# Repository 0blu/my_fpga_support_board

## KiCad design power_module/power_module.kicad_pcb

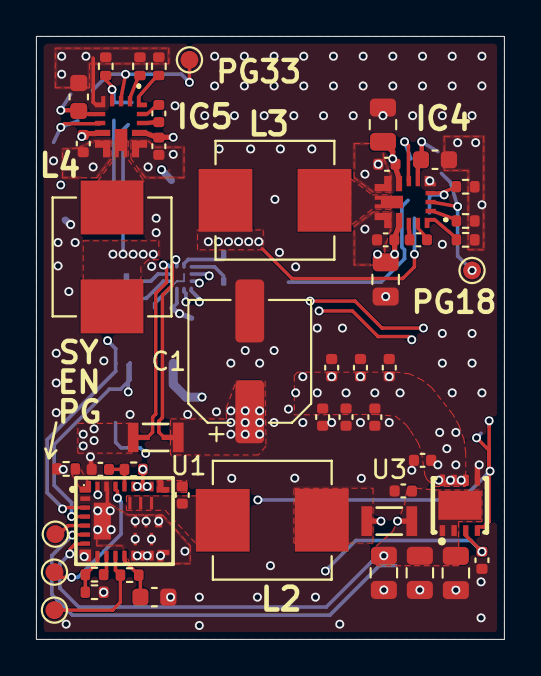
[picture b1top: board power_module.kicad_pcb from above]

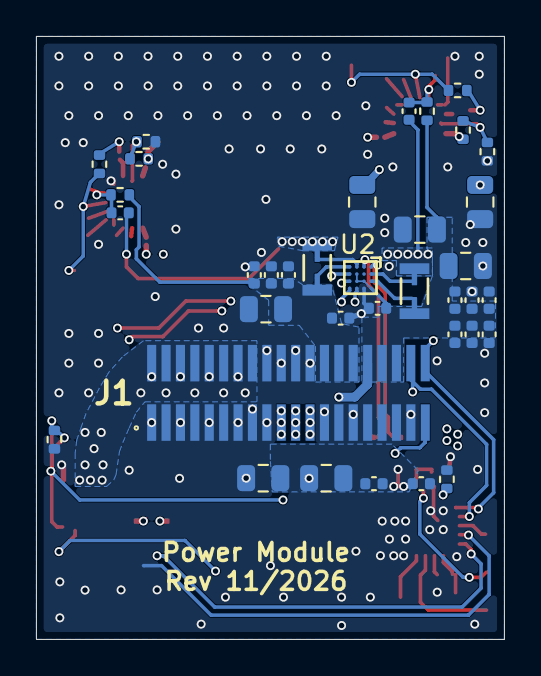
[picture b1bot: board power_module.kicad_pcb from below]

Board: 4 copper layers, 26.0 x 33.5 mm, 88 parts (37 on the bottom side), 49 nets.

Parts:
C1: 47uF 25V; CP_Elec_6.3x5.4
C22, C23, C29, C30, C36, C37: 10uF 25V; C_0805_2012Metric
C24: 1uF 25V; C_0402_1005Metric
C25, C33, C40: 4.7uF 16V; C_0603_1608Metric
C26, C27, C31, C32, C38, C39, C45, C46, C49, C50, C53, C54, C55, C56, C57, C59, C60, C62, C63, C64, C65, C72: 47nF 50V; C_0402_1005Metric
C28, C34, C41, C73, C74: 100nF 50V; C_0402_1005Metric
C35, C42: 20pF 50V; C_0402_1005Metric
C44, C47, C48: 22uF 10V; C_0805_2012Metric
C51, C52: 10uF 6.3V; C_0402_1005Metric
C75, C76, C77: 100uF 6.3V; C_0805_2012Metric
IC4, IC5: TPS543820RPYR
J1: FTE-120-01-G-DV
L2: 220nH; WE_L_744373460022
L3, L4: 1.0uH; WE_L_74437349010
NT1: NetTie_2; NetTie-2_SMD_Pad0.2mm
R24: 10R 1%; R_0402_1005Metric
R25, R39, R41, R46, R48: 10k 1%; R_0402_1005Metric
R27: 110k 0.1%; R_0402_1005Metric
R28: 20k 0.1%; R_0402_1005Metric
R29, R40: 26.1k 1%; R_0402_1005Metric
R30: 47.5k 1%; R_0402_1005Metric
R31, R32, R33, R34: 0.002R; shunt_1206in_3216mm
R35, R42: 16.9k 1%; R_0402_1005Metric
R36, R43: 6.8k 1%; R_0402_1005Metric
R37: 26.7k 1%; R_0402_1005Metric
R38, R45: 8.06k 1%; R_0402_1005Metric
R44: 60.4k 1%; R_0402_1005Metric
R47: 56k 1%; R_0402_1005Metric
R49: 100k 1%; R_0402_1005Metric
TP1: TP_PGDYN; TestPoint_Pad_D1.0mm
TP2: TP_EN; TestPoint_Pad_D1.0mm
TP3: TP_SYNC; TestPoint_Pad_D1.0mm
TP4: TP_PG3V3; TestPoint_Pad_D1.0mm
TP5: TP_PG1V8; TestPoint_Pad_D1.0mm
U1: TPS542A50
U2: INA4230AIYBJR
U3: TPS22959; TPS22959DNYR

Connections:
/+1.8V: C44.1, C45.1, C46.1, C59.1, C60.1, J1.26, J1.28, J1.30, R32.1, R40.2
/+3.3V: C47.1, C48.1, C49.1, C50.1, C62.1, C63.1, C64.1, C65.1, C73.1, C74.1, J1.32, J1.34, J1.36, R33.1, R47.2, U2.A4 (VS), U2.B3 (EN), U2.C2 (A0), U2.C3 (A1), U3.3 (VBIAS)
/+RAW_VIN: C1.1, J1.19, J1.21, J1.23, R31.4
/DYN_V: C72.1, C75.1, C76.1, C77.1, R34.1, U1.7 (RSP), U3.1 (VIN), U3.2 (VIN), U3.9 (VIN)
/DYN_V_EN: J1.39, R49.1, U3.4 (ON)
/DYN_V_EXT: C51.1, C52.1, C53.1, C54.1, C55.1, C56.1, C57.1, J1.2, J1.4, J1.6, J1.8, J1.10, J1.12, J1.14, J1.16, U3.6 (VOUT), U3.7 (VOUT), U3.8 (VOUT)
/Dynamic Power Conversion/+VIN: C22.1, C23.1, C26.1, C27.1, C29.1, C30.1, C31.1, C32.1, C36.1, C37.1, C38.1, C39.1, IC4.8 (VIN), IC4.12 (VIN_2), IC5.8 (VIN), IC5.12 (VIN_2), R24.1, R31.1, R35.2, R42.2, U1.18 (PVIN), U1.19 (PVIN), U1.20 (PVIN)
/Dynamic Power Conversion/BOOT: C28.1, U1.17 (BOOT)
/Dynamic Power Conversion/COMP: R29.2, U1.24 (COMP)
/Dynamic Power Conversion/DYN_RSN: NT1.1, U1.6 (RSN)
/Dynamic Power Conversion/EN: TP2.1 (1_1), U1.22 (EN)
/Dynamic Power Conversion/PGD: R25.2, TP1.1 (1_1), U1.11 (PGD)
/Dynamic Power Conversion/SREF: R27.2, U1.10 (SREF)
/Dynamic Power Conversion/SW: C28.2, L2.1, U1.26 (SW), U1.27 (SW), U1.28 (SW)
/Dynamic Power Conversion/SYNC: TP3.1 (1_1), U1.5 (SYNC)
/Dynamic Power Conversion/VREG: C25.1, R25.1, U1.12 (VREG)
/Dynamic Power Conversion/VSET: R27.1, R28.2, U1.9 (VSET)
/Measurement/MES_1.8_N: R32.2, U2.D1 (IN+3)
/Measurement/MES_1.8_P: R32.3, U2.C1 (IN–3)
/Measurement/MES_3.3_N: R33.2, U2.A3 (IN+1)
/Measurement/MES_3.3_P: R33.3, U2.A2 (IN–1)
/Measurement/MES_DYN_N: R34.2, U2.D2 (IN–4)
/Measurement/MES_DYN_P: R34.3, U2.D3 (IN+4)
/Measurement/MES_VIN_N: R31.2, U2.A1 (IN+2)
/Measurement/MES_VIN_P: R31.3, U2.B1 (IN–2)
/RAW_1.8V: C35.1, L3.2, R32.4
/RAW_3.3V: C42.1, L4.2, R33.4
/RAW_DYN_V: L2.2, R34.4
GND: C1.2, C22.2, C23.2, C24.2, C25.2, C26.2, C27.2, C29.2, C30.2, C31.2, C32.2, C33.2, C36.2, C37.2, C38.2, C39.2, C40.2, C44.2, C45.2, C46.2, C47.2, C48.2, C49.2, C50.2, C51.2, C52.2, C53.2, C54.2, C55.2, C56.2, C57.2, C59.2, C60.2, C62.2, C63.2, C64.2, C65.2, C72.2, C73.2, C74.2, C75.2, C76.2, C77.2, IC4.5 (AGND), IC4.9 (PGND), IC4.11 (PGND_2), IC4.16 (AGND_2), IC4.17 (PGND_3), IC4.20 (PGND_4), IC5.5 (AGND), IC5.9 (PGND), IC5.11 (PGND_2), IC5.16 (AGND_2), IC5.17 (PGND_3), IC5.20 (PGND_4), J1.1, J1.3, J1.5, J1.7, J1.9, J1.11, J1.13, J1.15, J1.17, J1.18, J1.20, J1.22, J1.24, J1.25, J1.27, J1.29, J1.31, J1.33, J1.35, J1.37, NT1.2, R28.1, R29.1, R30.1, R36.1, R37.1, R38.1, R41.1, R43.1, R44.1, R45.1, R48.1, R49.2, U1.2 (SS/PFM), U1.8 (AGND), U1.13 (PGND), U1.14 (PGND), U1.15 (PGND), U1.16 (PGND), U1.23 (FSEL), U1.25 (AGND), U1.29 (PGND), U1.30 (PGND), U1.31 (PGND), U1.32 (PGND), U1.33 (PGND), U2.B4 (GND), U3.5 (GND)
I2C_PM_SCL: J1.40, U1.3 (SCL), U2.C4 (SCL)
I2C_PM_SDA: J1.38, U1.4 (SDA), U2.D4 (SDA)
unnamed: C34.1, IC4.14 (BOOT)
unnamed: C33.1, IC4.6 (BP5), R39.1
unnamed: IC4.7 (EN), R35.1, R36.2
unnamed: C35.2, IC4.4 (FB), R40.1, R41.2
unnamed: IC4.2 (MODE), R37.2
unnamed: IC4.3 (PGOOD), R39.2, TP5.1 (1_1)
unnamed: C34.2, IC4.10 (SW), IC4.13 (SW_13), IC4.18 (SW_3), IC4.19 (SW_4), L3.1
unnamed: IC4.1 (SYNC/_FSEL), IC4.15 (SYNC/_FSEL_2), R38.2
unnamed: C41.1, IC5.14 (BOOT)
unnamed: C40.1, IC5.6 (BP5), R46.1
unnamed: IC5.7 (EN), R42.1, R43.2
unnamed: C42.2, IC5.4 (FB), R47.1, R48.2
unnamed: IC5.2 (MODE), R44.2
unnamed: IC5.3 (PGOOD), R46.2, TP4.1 (1_1)
unnamed: C41.2, IC5.10 (SW), IC5.13 (SW_13), IC5.18 (SW_3), IC5.19 (SW_4), L4.1
unnamed: IC5.1 (SYNC/_FSEL), IC5.15 (SYNC/_FSEL_2), R45.2
unnamed: C24.1, R24.2, U1.21 (AVIN)
unnamed: R30.2, U1.1 (ILIM)

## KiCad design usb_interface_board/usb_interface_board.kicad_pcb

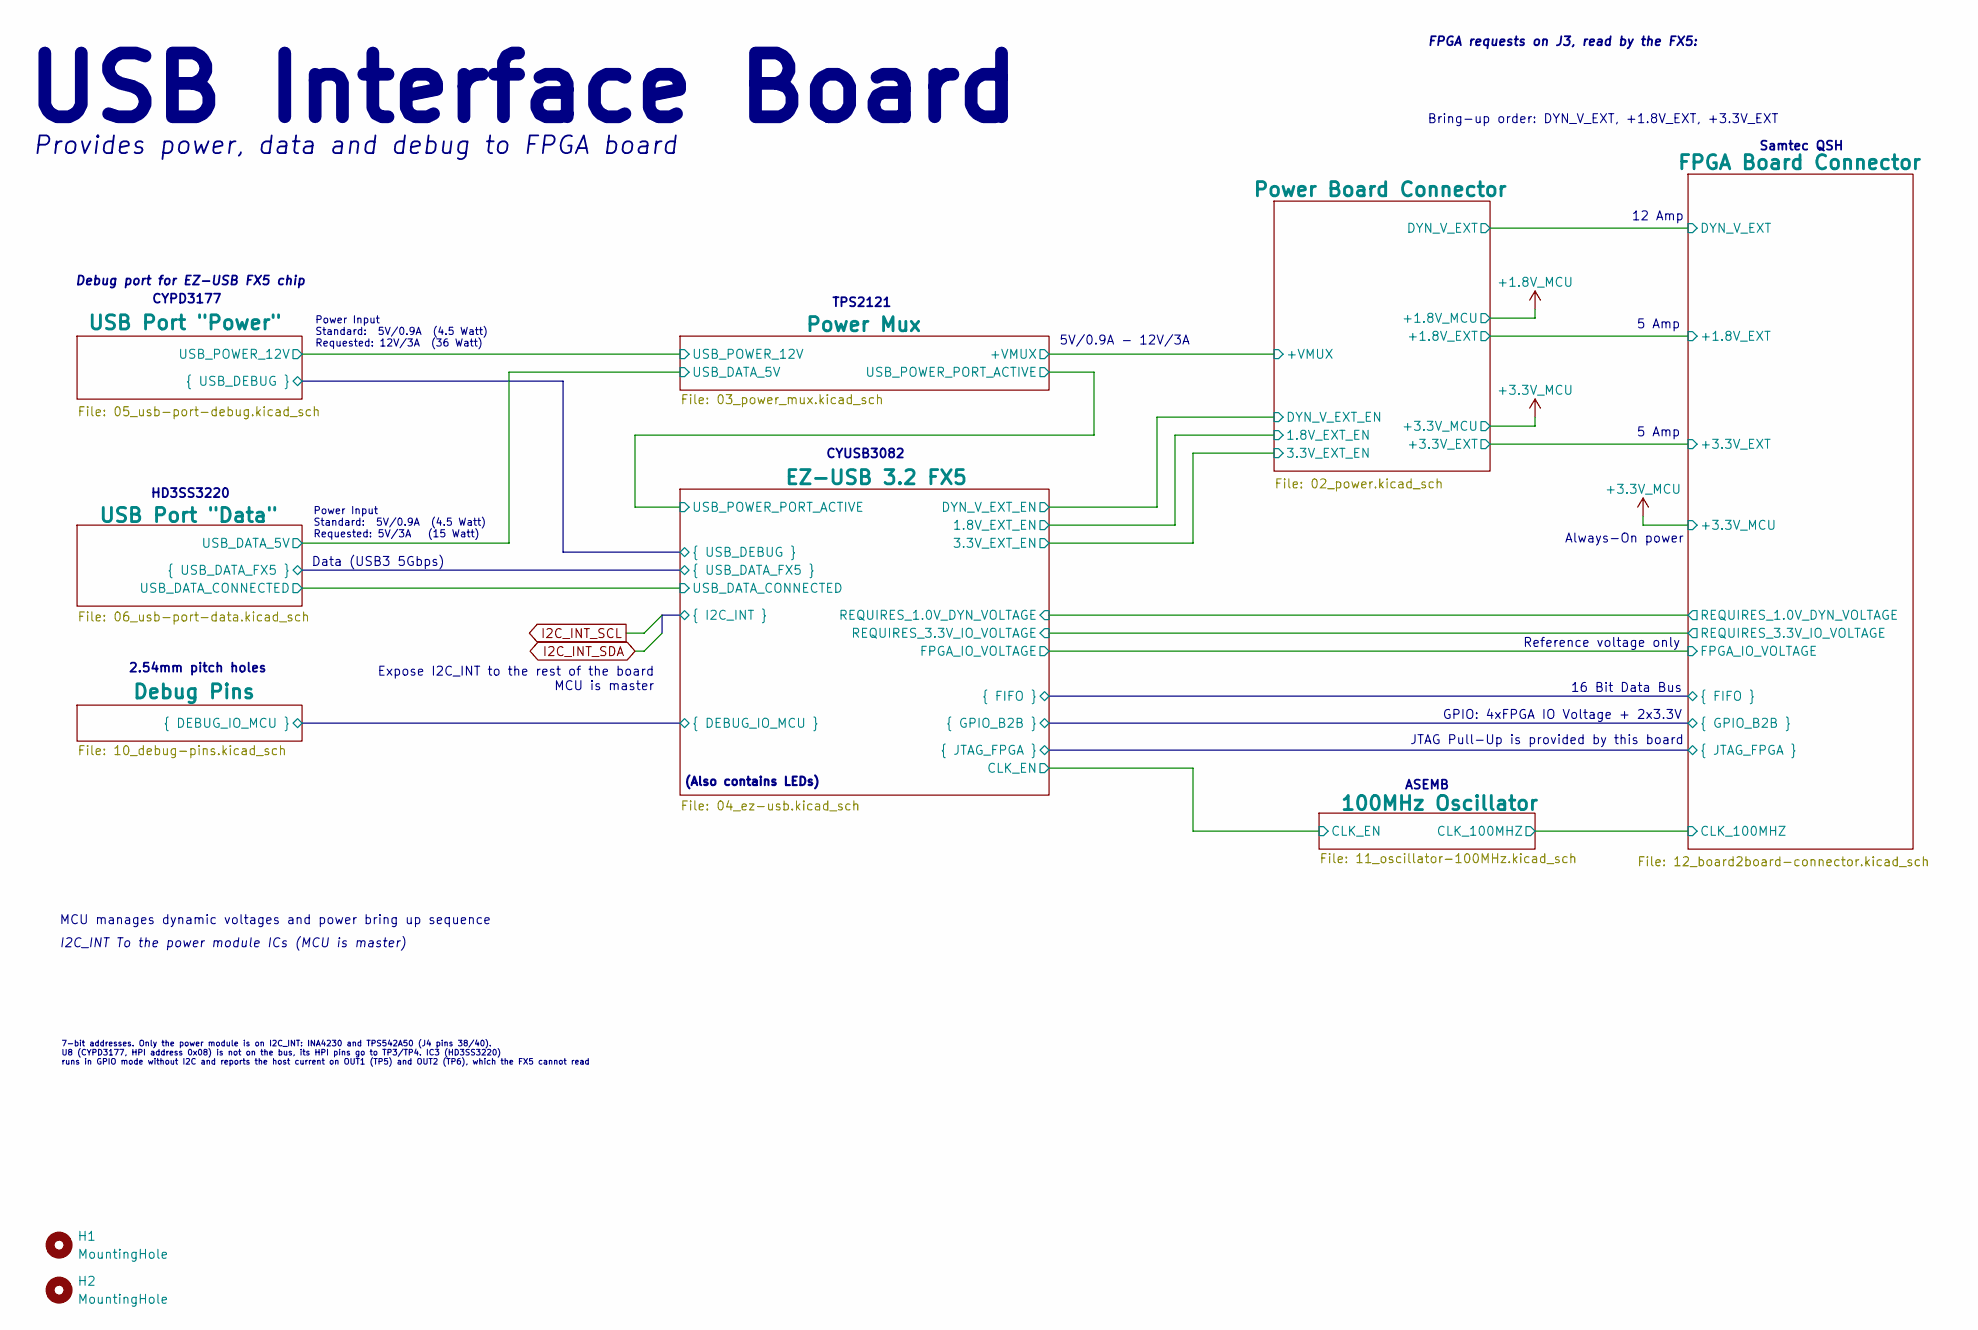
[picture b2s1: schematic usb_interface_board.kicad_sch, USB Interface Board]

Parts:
H1, H2: MountingHole; MountingHole_2.2mm_M2

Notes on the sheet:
MCU manages dynamic voltages and power bring up sequence
16 Bit Data Bus
ASEMB
Debug port for EZ-USB FX5 chip
(Also contains LEDs)
Power Input Standard: 5V/0.9A (4.5 Watt) Requested: 5V/3A (15 Watt)
CYUSB3082
USB Interface Board
Bring-up order: DYN_V_EXT, +1.8V_EXT, +3.3V_EXT
GPIO: 4xFPGA IO Voltage + 2x3.3V
Always-On power
Expose I2C_INT to the rest of the board MCU is master
CYPD3177
5 Amp
Samtec QSH
JTAG Pull-Up is provided by this board
2.54mm pitch holes
TPS2121
5V/0.9A - 12V/3A
Power Input Standard: 5V/0.9A (4.5 Watt) Requested: 12V/3A (36 Watt)
Reference voltage only
HD3SS3220
Data (USB3 5Gbps)
12 Amp
FPGA requests on J3, read by the FX5:
Provides power, data and debug to FPGA board
I2C_INT To the power module ICs (MCU is master)
7-bit addresses. Only the power module is on I2C_INT: INA4230 and TPS542A50 (J4 pins 38/40). U8 (CYPD3177, HPI address 0x08) is not on the bus, its HPI pins go to TP3/TP4. IC3 (HD3SS3220) runs in GPIO mode without I2C and reports the host current on OUT1 (TP5) and OUT2 (TP6), which the FX5 cannot r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

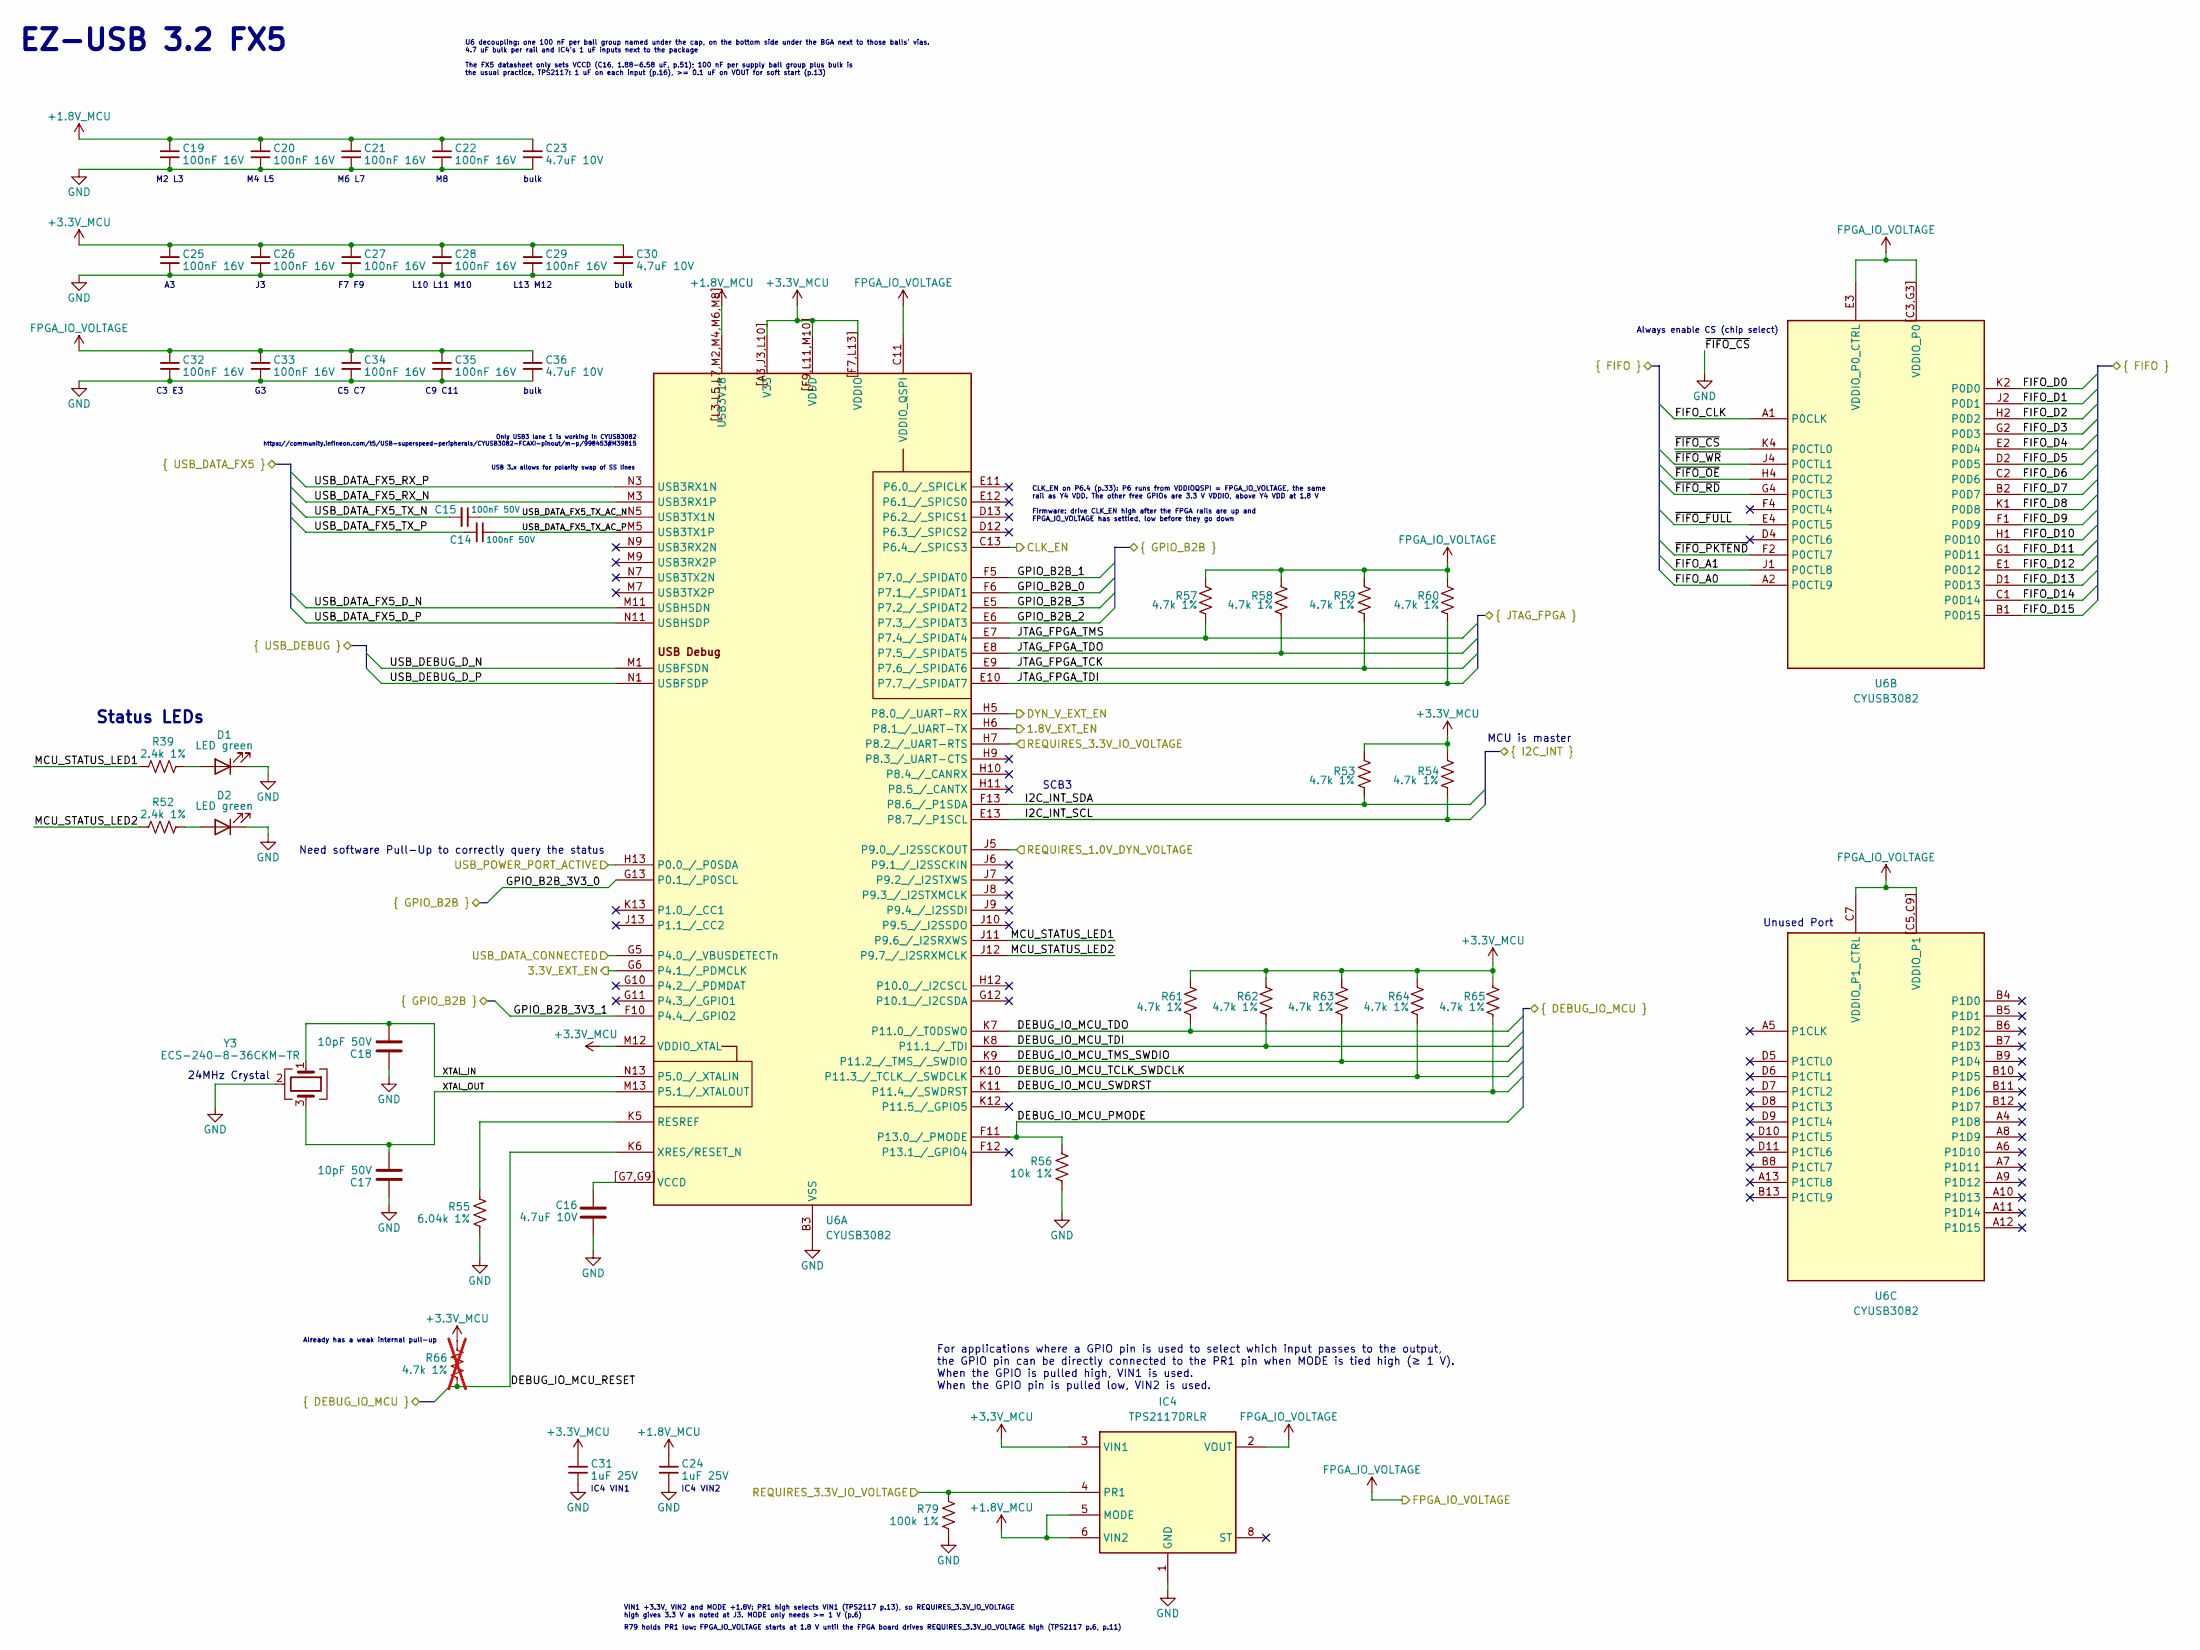
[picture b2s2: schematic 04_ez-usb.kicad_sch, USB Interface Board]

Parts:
C14, C15: 100nF 50V; C_0402_1005Metric; Manufacturer Part CL05B104KB54PNC; LCSC C307331
C16, C23, C30, C36: 4.7uF 10V; C_0402_1005Metric; Manufacturer Part CL05A475MP5NRNC; LCSC C23733
C17, C18: 10pF 50V; C_0402_1005Metric; Manufacturer Part CL05C100JB5NNNC; LCSC C32949
C19, C20, C21, C22, C25, C26, C27, C28, C29, C32, C33, C34, C35: 100nF 16V; C_0201_0603Metric; Manufacturer Part CL03A104KO3NNNC; LCSC C307380
C24, C31: 1uF 25V; C_0402_1005Metric; Manufacturer Part CL05A105KA5NQNC; LCSC C52923
D1, D2: LED green; LED_0805_2012Metric; Manufacturer Part LTST-C170KGKT; LCSC C98221
IC4: TPS2117DRLR; SOTFL50P160X60-8N; Mouser Part Number 595-TPS2117DRLR
R39, R52: 2.4k 1%; R_0402_1005Metric; Manufacturer Part RC0402FR-072K4L; LCSC C112296
R53, R54, R57, R58, R59, R60, R61, R62, R63, R64, R65: 4.7k 1%; R_0402_1005Metric; Manufacturer Part 0402WGF4701TCE; LCSC C25900
R55: 6.04k 1%; R_0402_1005Metric; Manufacturer Part RC0402FR-076K04L; LCSC C97819
R56: 10k 1%; R_0402_1005Metric; Manufacturer Part 0402WGF1002TCE; LCSC C25744
R66: 4.7k 1%; R_0402_1005Metric; Manufacturer Part 0402WGF4701TCE; LCSC C25900; not fitted
R79: 100k 1%; R_0402_1005Metric; Manufacturer Part 0402WGF1003TCE; LCSC C25741
U6: CYUSB3082; Infineon_TFBGA-169_10x10mm_Layout13x13_P0.75mm; Manufacturer Part CYUSB3082-FCAXI
Y3: ECS-240-8-36CKM-TR; Manufacturer Part ECS-240-8-36CKM-TR; LCSC C435195

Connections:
+1.8V_MCU: C19.1, C20.1, C21.1, C22.1, C23.1, C24.1, IC4.5 (MODE), IC4.6 (VIN2), U6.L3 (USB3V18), U6.L5 (USB3V18), U6.L7 (USB3V18), U6.M2 (USB3V18), U6.M4 (USB3V18), U6.M6 (USB3V18), U6.M8 (USB3V18), U6.[L3,L5,L7,M2,M4,M6,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 (USB3V18); also elsewhere on the board
+3.3V_MCU: C25.1, C26.1, C27.1, C28.1, C29.1, C30.1, C31.1, IC4.3 (VIN1), R53.1, R54.1, R61.1, R62.1, R63.1, R64.1, R65.1, R66.1, U6.A3 (V33), U6.F7 (VDDIO), U6.F9 (VDDD), U6.J3 (V33), U6.L10 (V33), U6.L11 (VDDD), U6.L13 (VDDIO), U6.M10 (VDDD), U6.M12 (VDDIO_XTAL), U6.[A3,J3,L10] (V33), U6.[F7,L13] (VDDIO), U6.[F9,L11,M10] (VDDD); also elsewhere on the board
/100MHz Oscillator/CLK_EN: U6.C13 (P6.4_/_SPICS3); also elsewhere on the board
/Debug Pins/DEBUG_IO_MCU_PMODE: R56.1, U6.F11 (P13.0_/_PMODE); also elsewhere on the board
/Debug Pins/DEBUG_IO_MCU_RESET: R66.2, U6.K6 (XRES/RESET_N); also elsewhere on the board
/Debug Pins/DEBUG_IO_MCU_SWDRST: R65.2, U6.K11 (P11.4_/_SWDRST); also elsewhere on the board
/Debug Pins/DEBUG_IO_MCU_TCLK_SWDCLK: R64.2, U6.K10 (P11.3_/_TCLK_/_SWDCLK); also elsewhere on the board
/Debug Pins/DEBUG_IO_MCU_TDI: R62.2, U6.K8 (P11.1_/_TDI); also elsewhere on the board
/Debug Pins/DEBUG_IO_MCU_TDO: R61.2, U6.K7 (P11.0_/_T0DSWO); also elsewhere on the board
/Debug Pins/DEBUG_IO_MCU_TMS_SWDIO: R63.2, U6.K9 (P11.2_/_TMS_/_SWDIO); also elsewhere on the board
/EZ-USB 3.2 FX5/1.8V_EXT_EN: U6.H6 (P8.1_/_UART-TX); also elsewhere on the board
/EZ-USB 3.2 FX5/3.3V_EXT_EN: U6.G6 (P4.1_/_PDMCLK); also elsewhere on the board
/EZ-USB 3.2 FX5/DYN_V_EXT_EN: U6.H5 (P8.0_/_UART-RX); also elsewhere on the board
/EZ-USB 3.2 FX5/FIFO_A0: U6.A2 (P0CTL9); also elsewhere on the board
/EZ-USB 3.2 FX5/FIFO_A1: U6.J1 (P0CTL8); also elsewhere on the board
/EZ-USB 3.2 FX5/FIFO_CLK: U6.A1 (P0CLK); also elsewhere on the board
/EZ-USB 3.2 FX5/FIFO_D0: U6.K2 (P0D0); also elsewhere on the board
/EZ-USB 3.2 FX5/FIFO_D1: U6.J2 (P0D1); also elsewhere on the board
/EZ-USB 3.2 FX5/FIFO_D2: U6.H2 (P0D2); also elsewhere on the board
/EZ-USB 3.2 FX5/FIFO_D3: U6.G2 (P0D3); also elsewhere on the board
/EZ-USB 3.2 FX5/FIFO_D4: U6.E2 (P0D4); also elsewhere on the board
/EZ-USB 3.2 FX5/FIFO_D5: U6.D2 (P0D5); also elsewhere on the board
/EZ-USB 3.2 FX5/FIFO_D6: U6.C2 (P0D6); also elsewhere on the board
/EZ-USB 3.2 FX5/FIFO_D7: U6.B2 (P0D7); also elsewhere on the board
/EZ-USB 3.2 FX5/FIFO_D8: U6.K1 (P0D8); also elsewhere on the board
/EZ-USB 3.2 FX5/FIFO_D9: U6.F1 (P0D9); also elsewhere on the board
/EZ-USB 3.2 FX5/FIFO_D10: U6.H1 (P0D10); also elsewhere on the board
/EZ-USB 3.2 FX5/FIFO_D11: U6.G1 (P0D11); also elsewhere on the board
/EZ-USB 3.2 FX5/FIFO_D12: U6.E1 (P0D12); also elsewhere on the board
/EZ-USB 3.2 FX5/FIFO_D13: U6.D1 (P0D13); also elsewhere on the board
/EZ-USB 3.2 FX5/FIFO_D14: U6.C1 (P0D14); also elsewhere on the board
/EZ-USB 3.2 FX5/FIFO_D15: U6.B1 (P0D15); also elsewhere on the board
/EZ-USB 3.2 FX5/GPIO_B2B_0: U6.F6 (P7.1_/_SPIDAT1); also elsewhere on the board
/EZ-USB 3.2 FX5/GPIO_B2B_1: U6.F5 (P7.0_/_SPIDAT0); also elsewhere on the board
/EZ-USB 3.2 FX5/GPIO_B2B_2: U6.E6 (P7.3_/_SPIDAT3); also elsewhere on the board
/EZ-USB 3.2 FX5/GPIO_B2B_3: U6.E5 (P7.2_/_SPIDAT2); also elsewhere on the board
/EZ-USB 3.2 FX5/GPIO_B2B_3V3_0: U6.G13 (P0.1_/_P0SCL); also elsewhere on the board
/EZ-USB 3.2 FX5/GPIO_B2B_3V3_1: U6.F10 (P4.4_/_GPIO2); also elsewhere on the board
/EZ-USB 3.2 FX5/JTAG_FPGA_TCK: R59.2, U6.E9 (P7.6_/_SPIDAT6); also elsewhere on the board
/EZ-USB 3.2 FX5/JTAG_FPGA_TDI: R60.2, U6.E10 (P7.7_/_SPIDAT7); also elsewhere on the board
/EZ-USB 3.2 FX5/JTAG_FPGA_TDO: R58.2, U6.E8 (P7.5_/_SPIDAT5); also elsewhere on the board
/EZ-USB 3.2 FX5/JTAG_FPGA_TMS: R57.2, U6.E7 (P7.4_/_SPIDAT4); also elsewhere on the board
/EZ-USB 3.2 FX5/MCU_STATUS_LED1: R39.2, U6.J11 (P9.6_/_I2SRXWS)
/EZ-USB 3.2 FX5/MCU_STATUS_LED2: R52.2, U6.J12 (P9.7_/_I2SRXMCLK)
/EZ-USB 3.2 FX5/REQUIRES_1.0V_DYN_VOLTAGE: U6.J5 (P9.0_/_I2SSCKOUT); also elsewhere on the board
/EZ-USB 3.2 FX5/REQUIRES_3.3V_IO_VOLTAGE: IC4.4 (PR1), R79.1, U6.H7 (P8.2_/_UART-RTS); also elsewhere on the board
/EZ-USB 3.2 FX5/USB_DATA_CONNECTED: U6.G5 (P4.0_/_VBUSDETECTn); also elsewhere on the board
/EZ-USB 3.2 FX5/USB_DATA_FX5_D_N: U6.M11 (USBHSDN); also elsewhere on the board
/EZ-USB 3.2 FX5/USB_DATA_FX5_D_P: U6.N11 (USBHSDP); also elsewhere on the board
/EZ-USB 3.2 FX5/USB_DATA_FX5_RX_N: U6.M3 (USB3RX1P); also elsewhere on the board
/EZ-USB 3.2 FX5/USB_DATA_FX5_RX_P: U6.N3 (USB3RX1N); also elsewhere on the board
/EZ-USB 3.2 FX5/USB_DATA_FX5_TX_AC_N: C15.2, U6.N5 (USB3TX1N)
/EZ-USB 3.2 FX5/USB_DATA_FX5_TX_AC_P: C14.2, U6.M5 (USB3TX1P)
/EZ-USB 3.2 FX5/USB_DATA_FX5_TX_N: C15.1; also elsewhere on the board
/EZ-USB 3.2 FX5/USB_DATA_FX5_TX_P: C14.1; also elsewhere on the board
/EZ-USB 3.2 FX5/USB_DEBUG_D_N: U6.M1 (USBFSDN); also elsewhere on the board
/EZ-USB 3.2 FX5/USB_DEBUG_D_P: U6.N1 (USBFSDP); also elsewhere on the board
/EZ-USB 3.2 FX5/USB_POWER_PORT_ACTIVE: U6.H13 (P0.0_/_P0SDA); also elsewhere on the board
/EZ-USB 3.2 FX5/XTAL_IN: C18.2, U6.N13 (P5.0_/_XTALIN), Y3.1
/EZ-USB 3.2 FX5/XTAL_OUT: C17.2, U6.M13 (P5.1_/_XTALOUT), Y3.3
/EZ-USB 3.2 FX5/~FIFO_FULL: U6.E4 (P0CTL5); also elsewhere on the board
/EZ-USB 3.2 FX5/~FIFO_OE: U6.H4 (P0CTL2); also elsewhere on the board
/EZ-USB 3.2 FX5/~FIFO_PKTEND: U6.F2 (P0CTL7); also elsewhere on the board
/EZ-USB 3.2 FX5/~FIFO_RD: U6.G4 (P0CTL3); also elsewhere on the board
/EZ-USB 3.2 FX5/~FIFO_WR: U6.J4 (P0CTL1); also elsewhere on the board
FPGA_IO_VOLTAGE: C32.1, C33.1, C34.1, C35.1, C36.1, IC4.2 (VOUT), IC4.7 (VOUT_2), R57.1, R58.1, R59.1, R60.1, U6.C3 (VDDIO_P0), U6.C5 (VDDIO_P1), U6.C7 (VDDIO_P1_CTRL), U6.C9 (VDDIO_P1), U6.C11 (VDDIO_QSPI), U6.E3 (VDDIO_P0_CTRL), U6.G3 (VDDIO_P0), U6.[C3,G3] (VDDIO_P0), U6.[C5,C9] (VDDIO_P1); also elsewhere on the board
GND: C16.1, C17.1, C18.1, C19.2, C20.2, C21.2, C22.2, C23.2, C24.2, C25.2, C26.2, C27.2, C28.2, C29.2, C30.2, C31.2, C32.2, C33.2, C34.2, C35.2, C36.2, D1.1 (K), D2.1 (K), IC4.1 (GND), R55.2, R56.2, R79.2, U6.B3 (VSS), U6.C4 (VSS), U6.C6 (VSS), U6.C8 (VSS), U6.C10 (VSS), U6.C12 (VSS), U6.D3 (VSS), U6.F3 (VSS), U6.F8 (VSS), U6.G8 (VSS), U6.H3 (VSS), U6.H8 (VSS), U6.K3 (VSS), U6.K4 (P0CTL0), U6.L1 (VSS), U6.L2 (VSS), U6.L4 (VSS), U6.L6 (VSS), U6.L8 (VSS), U6.L9 (VSS), U6.L12 (VSS), U6.N2 (VSS), U6.N4 (VSS), U6.N6 (VSS), U6.N8 (VSS), U6.N10 (VSS), U6.N12 (VSS), Y3.2 (G), Y3.4 (G); also elsewhere on the board
I2C_INT_SCL: R54.2, U6.E13 (P8.7_/_P1SCL); also elsewhere on the board
I2C_INT_SDA: R53.2, U6.F13 (P8.6_/_P1SDA); also elsewhere on the board
unnamed: D1.2 (A), R39.1
unnamed: D2.2 (A), R52.1
unnamed: R55.1, U6.K5 (RESREF)
unnamed: C16.2, U6.G7 (VCCD), U6.G9 (VCCD), U6.[G7,G9] (VCCD)

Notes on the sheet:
L13 M12
Always enable CS (chip select)
Only USB3 lane 1 is working in CYUSB3082 https://community.infineon.com/t5/USB-superspeed-peripherals/CYUSB3082-FCAXI-pinout/m-p/998453#M39815
24MHz Crystal
Status LEDs
CLK_EN on P6.4 (p.33): P6 runs from VDDIOQSPI = FPGA_IO_VOLTAGE, the same rail as Y4 VDD. The other free GPIOs are 3.3 V VDDIO, above Y4 VDD at 1.8 V
Firmware: drive CLK_EN high after the FPGA rails are up and FPGA_IO_VOLTAGE has settled, low before they go down
L10 L11 M10
SCB3
F7 F9
M4 L5
M6 L7
The FX5 datasheet only sets VCCD (C16, 1.88-6.58 uF, p.51); 100 nF per supply ball group plus bulk is the usual practice. TPS2117: 1 uF on each input (p.16), >= 0.1 uF on VOUT for soft start (p.13)
M2 L3
Need software Pull-Up to correctly query the status
C9 C11
USB 3.x allows for polarity swap of SS lines
C3 E3
R79 holds PR1 low: FPGA_IO_VOLTAGE starts at 1.8 V until the FPGA board drives REQUIRES_3.3V_IO_VOLTAGE high (TPS2117 p.6, p.11)
MCU is master
bulk
EZ-USB 3.2 FX5
VIN1 +3.3V, VIN2 and MODE +1.8V: PR1 high selects VIN1 (TPS2117 p.13), so REQUIRES_3.3V_IO_VOLTAGE high gives 3.3 V as noted at J3. MODE only needs >= 1 V (p.6)
IC4 VIN1
Already has a weak internal pull-up
C5 C7
For applications where a GPIO pin is used to select which input passes to the output, the GPIO pin can be directly connected to the PR1 pin when MODE is tied high (≥ 1 V). When the GPIO is pulled high, VIN1 is used. When the GPIO pin is pulled low, VIN2 is used.
U6 decoupling: one 100 nF per ball group named under the cap, on the bottom side under the BGA next to those balls' vias. 4.7 uF bulk per rail and IC4's 1 uF inputs next to the package
Unused Port
IC4 VIN2

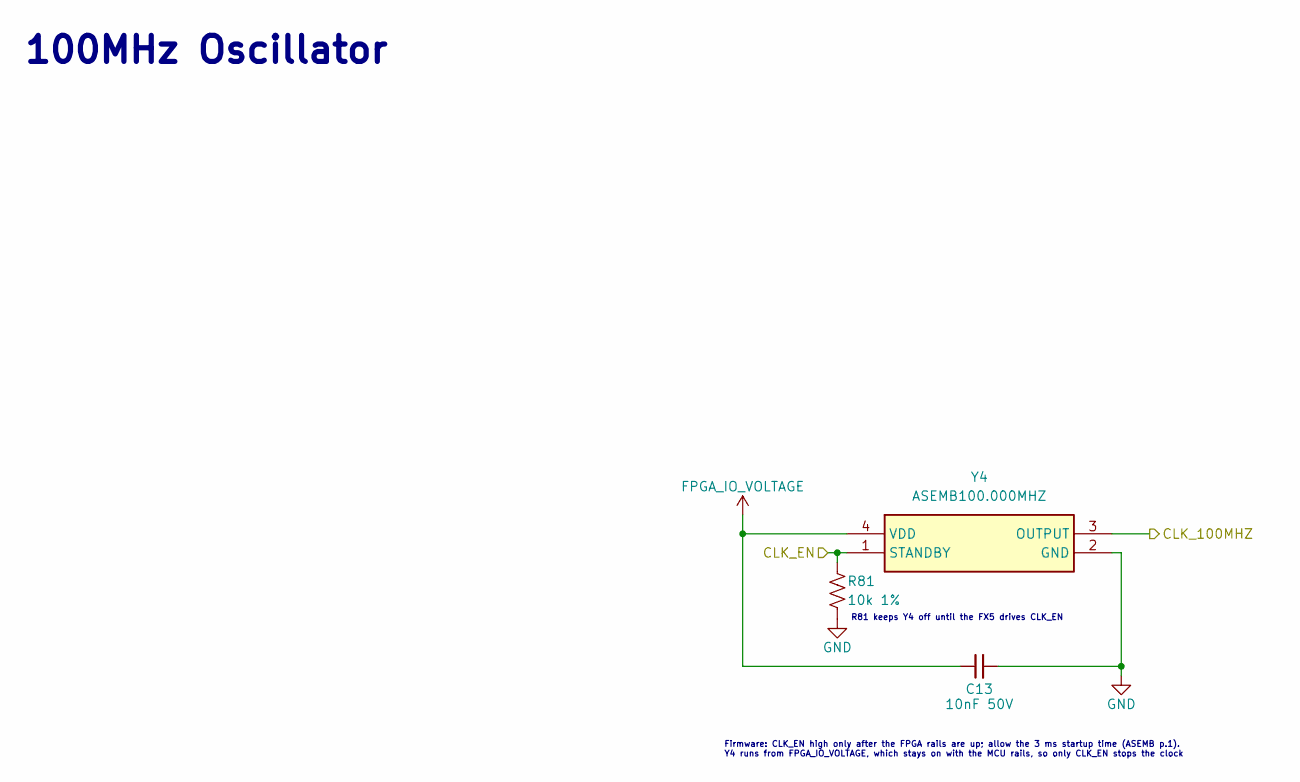
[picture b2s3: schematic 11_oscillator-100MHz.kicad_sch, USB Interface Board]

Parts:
C13: 10nF 50V; C_0402_1005Metric; Manufacturer Part CL05B103KB5NNNC; LCSC C15195
R81: 10k 1%; R_0402_1005Metric; Manufacturer Part 0402WGF1002TCE; LCSC C25744
Y4: ASEMB100.000MHZ; ASEMB; Manufacturer Part ASEMB-100.000MHZ-XY-T; LCSC C1987210

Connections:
/100MHz Oscillator/CLK_100MHZ: Y4.3 (OUTPUT); also elsewhere on the board
/100MHz Oscillator/CLK_EN: R81.1, Y4.1 (STANDBY); also elsewhere on the board
FPGA_IO_VOLTAGE: C13.2, Y4.4 (VDD); also elsewhere on the board
GND: C13.1, R81.2, Y4.2 (GND); also elsewhere on the board

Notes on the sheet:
R81 keeps Y4 off until the FX5 drives CLK_EN
100MHz Oscillator
Firmware: CLK_EN high only after the FPGA rails are up; allow the 3 ms startup time (ASEMB p.1). Y4 runs from FPGA_IO_VOLTAGE, which stays on with the MCU rails, so only CLK_EN stops the clock

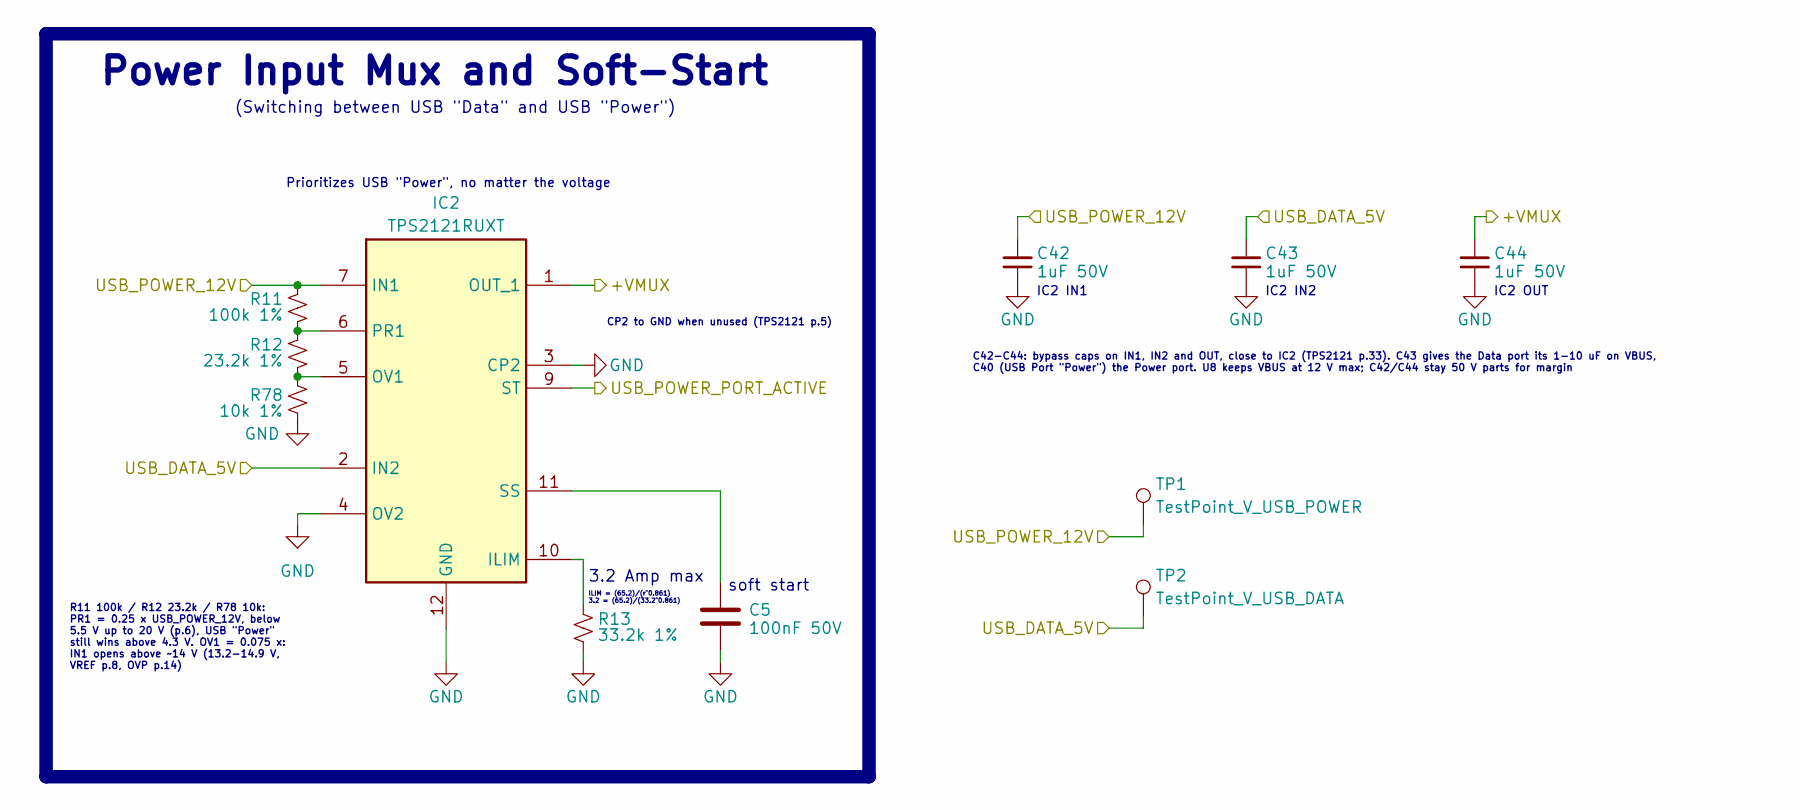
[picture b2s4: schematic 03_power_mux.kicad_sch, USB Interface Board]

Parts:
C5: 100nF 50V; C_0402_1005Metric; Manufacturer Part CL05B104KB54PNC; LCSC C307331
C42, C43, C44: 1uF 50V; C_0603_1608Metric; Manufacturer Part CL10A105KB8NNNC; LCSC C15849
IC2: TPS2121RUXT; Mouser Part Number 595-TPS2121RUXT
R11: 100k 1%; R_0402_1005Metric; Manufacturer Part 0402WGF1003TCE; LCSC C25741
R12: 23.2k 1%; R_0402_1005Metric; Manufacturer Part CRCW040223K2FKED; LCSC C2076557
R13: 33.2k 1%; R_0402_1005Metric; Manufacturer Part CRCW040233K2FKED; LCSC C844106
R78: 10k 1%; R_0402_1005Metric; Manufacturer Part 0402WGF1002TCE; LCSC C25744
TP1: TestPoint_V_USB_POWER; TestPoint_Pad_D1.0mm
TP2: TestPoint_V_USB_DATA; TestPoint_Pad_D1.0mm

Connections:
/EZ-USB 3.2 FX5/USB_DATA_5V: C43.1, IC2.2 (IN2), TP2.1 (1_1); also elsewhere on the board
/EZ-USB 3.2 FX5/USB_POWER_PORT_ACTIVE: IC2.9 (ST); also elsewhere on the board
/Power Board Connector/+VMUX: C44.1, IC2.1 (OUT_1), IC2.8 (OUT_2); also elsewhere on the board
/USB Port "Power"/USB_POWER_12V: C42.1, IC2.7 (IN1), R11.1, TP1.1 (1_1); also elsewhere on the board
GND: C5.2, C42.2, C43.2, C44.2, IC2.3 (CP2), IC2.4 (OV2), IC2.12 (GND), R13.2, R78.2; also elsewhere on the board
unnamed: IC2.10 (ILIM), R13.1
unnamed: IC2.5 (OV1), R12.2, R78.1
unnamed: IC2.6 (PR1), R11.2, R12.1
unnamed: C5.1, IC2.11 (SS)

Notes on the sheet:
IC2 OUT
CP2 to GND when unused (TPS2121 p.5)
Power Input Mux and Soft-Start
IC2 IN2
C42-C44: bypass caps on IN1, IN2 and OUT, close to IC2 (TPS2121 p.33). C43 gives the Data port its 1-10 uF on VBUS, C40 (USB Port "Power") the Power port. U8 keeps VBUS at 12 V max; C42/C44 stay 50 V parts for margin
R11 100k / R12 23.2k / R78 10k: PR1 = 0.25 x USB_POWER_12V, below 5.5 V up to 20 V (p.6), USB "Power" still wins above 4.3 V. OV1 = 0.075 x: IN1 opens above ~14 V (13.2-14.9 V, VREF p.8, OVP p.14)
ILIM = (65.2)/(r^0.861) 3.2 = (65.2)/(33.2^0.861)
Prioritizes USB "Power", no matter the voltage
(Switching between USB "Data" and USB "Power")
IC2 IN1
soft start
3.2 Amp max
